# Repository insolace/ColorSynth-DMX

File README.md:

# ColorSynth-DMX<br>
163 DMX RGB pixels for a Burningman 2013 geodesic dome located at camp Morning Cookie<br>
Designed and assembled by Eric Bateman<br>
BMP to DMX mapping done in collaboration with Craig Dorety (http://craigdorety.com/)<br>

ColorSynth DMX RGX pixels are three channel DMX fixtures.  Programmed in assembly, the channels are software defined.

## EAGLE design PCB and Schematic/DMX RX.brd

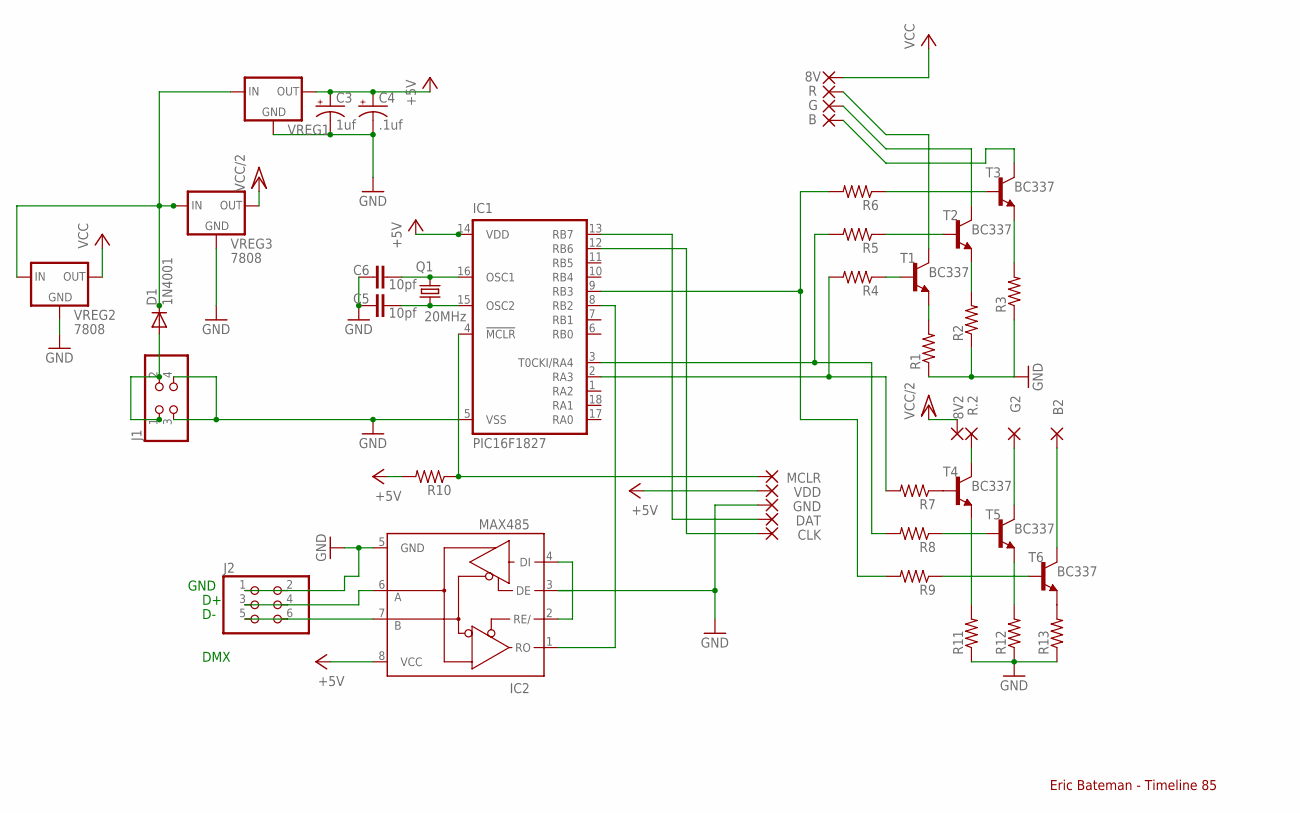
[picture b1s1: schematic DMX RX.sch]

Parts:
8V, 8V2: 2,15/1,0
B, B2: 2,15/1,0
C3: 1uf; E2,5-7
C4: .1uf; E2,5-7
C5, C6: 10pf; C5B3.5
CLK: 1,6/0,8
D1: 1N4001; DIODE-1N4001
DAT: 1,6/0,8
G, G2: 2,15/1,0
GND: 1,6/0,8
IC1: PIC16F1827; DIL18
IC2: MAX485; DIL08
J1: PINHD-2X2/90; 2X02/90
J2: PINHD-2X3/90; 2X03/90
MCLR: 1,6/0,8
Q1: 20MHz; HC49/S
R, R.2: 2,15/1,0
R1, R2, R3, R11, R12, R13: R-US_0411/12; 0411/12
R4, R5, R6, R7, R8, R9, R10: R-US_0204/7; 0204/7
T1, T2, T3, T4, T5, T6: BC337; TO92
VDD: 1,6/0,8
VREG1: 78LXX
VREG2, VREG3: 7808; 78XXS

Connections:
+5V: C3.+, C4.+, IC1.14 (VDD), IC2.8 (VCC), R10.2, VDD.1, VREG1.OUT
+12V: D1.C, VREG1.IN, VREG2.IN, VREG3.IN
A: IC2.6 (A), J2.3, J2.4
B: IC2.7 (B), J2.5, J2.6
CLK: CLK.1, IC1.12 (RB6)
DAT: DAT.1, IC1.13 (RB7)
DC-IN: D1.A, J1.1, J1.2
GND: C3.-, C4.-, C5.2, C6.2, GND.1, IC1.5 (VSS), IC2.2 (RE/), IC2.3 (DE), IC2.4 (DI), IC2.5 (GND), J1.3, J1.4, J2.1, J2.2, R1.1, R2.1, R3.1, R11.1, R12.1, R13.1, VREG1.GND, VREG2.GND, VREG3.GND
MCLR: IC1.4 (!MCLR), MCLR.1, R10.1
unnamed: R6.1, T3.2 (B)
unnamed: R3.2, T3.1 (E)
unnamed: R1.2, T1.1 (E)
unnamed: C6.1, IC1.16 (OSC1), Q1.1
unnamed: C5.1, IC1.15 (OSC2), Q1.2
unnamed: IC1.2 (RA3), R4.2, R7.2
unnamed: IC1.3 (T0CKI/RA4), R5.2, R8.2
unnamed: IC1.9 (RB3), R6.2, R9.2
unnamed: R5.1, T2.2 (B)
unnamed: R4.1, T1.2 (B)
unnamed: R.1, T1.3 (C)
unnamed: G.1, T2.3 (C)
unnamed: R2.2, T2.1 (E)
unnamed: R7.1, T4.2 (B)
unnamed: R13.2, T6.1 (E)
unnamed: R12.2, T5.1 (E)
unnamed: R11.2, T4.1 (E)
unnamed: R9.1, T6.2 (B)
unnamed: R8.1, T5.2 (B)
unnamed: G2.1, T5.3 (C)
unnamed: B2.1, T6.3 (C)
unnamed: R.2.1, T4.3 (C)
unnamed: B.1, T3.3 (C)
RX: IC1.8 (RB2), IC2.1 (RO)
VCC: 8V.1, VREG2.OUT
VCC/2: 8V2.1, VREG3.OUT

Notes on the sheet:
GND
DMX
Eric Bateman - Timeline 85

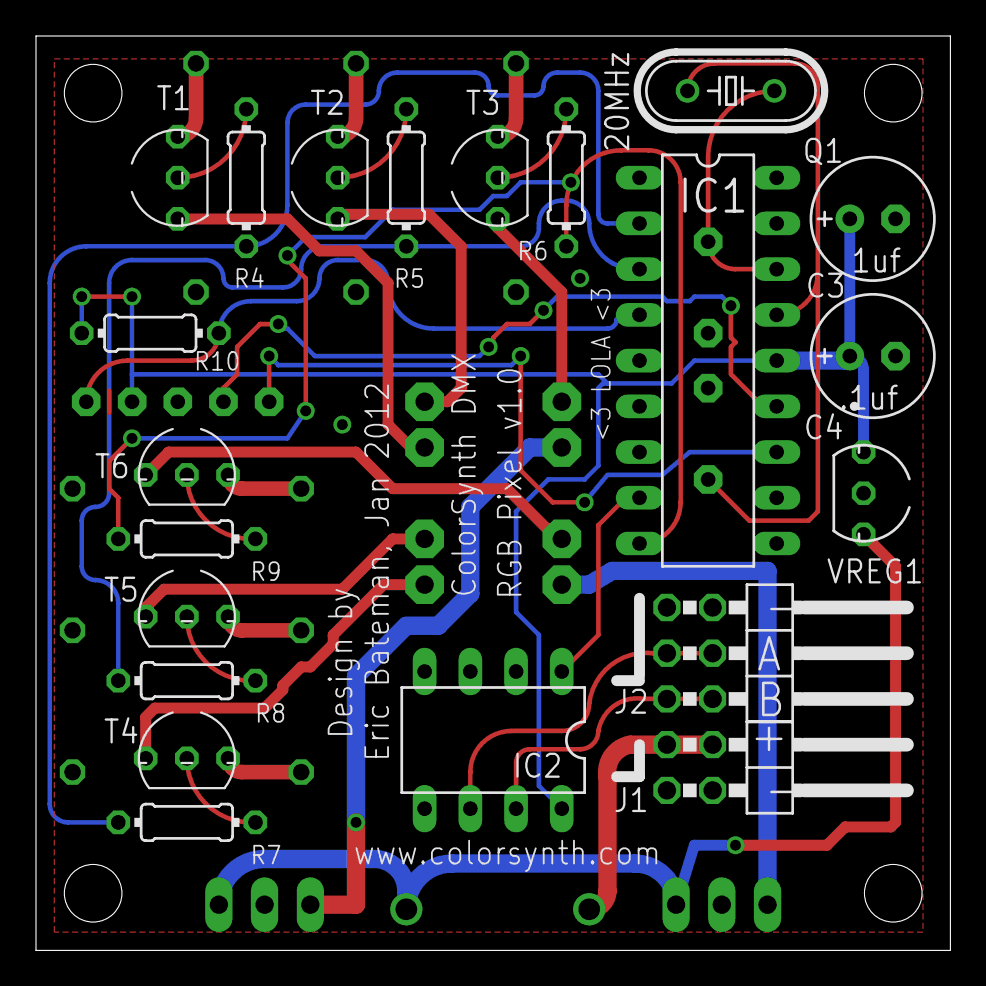
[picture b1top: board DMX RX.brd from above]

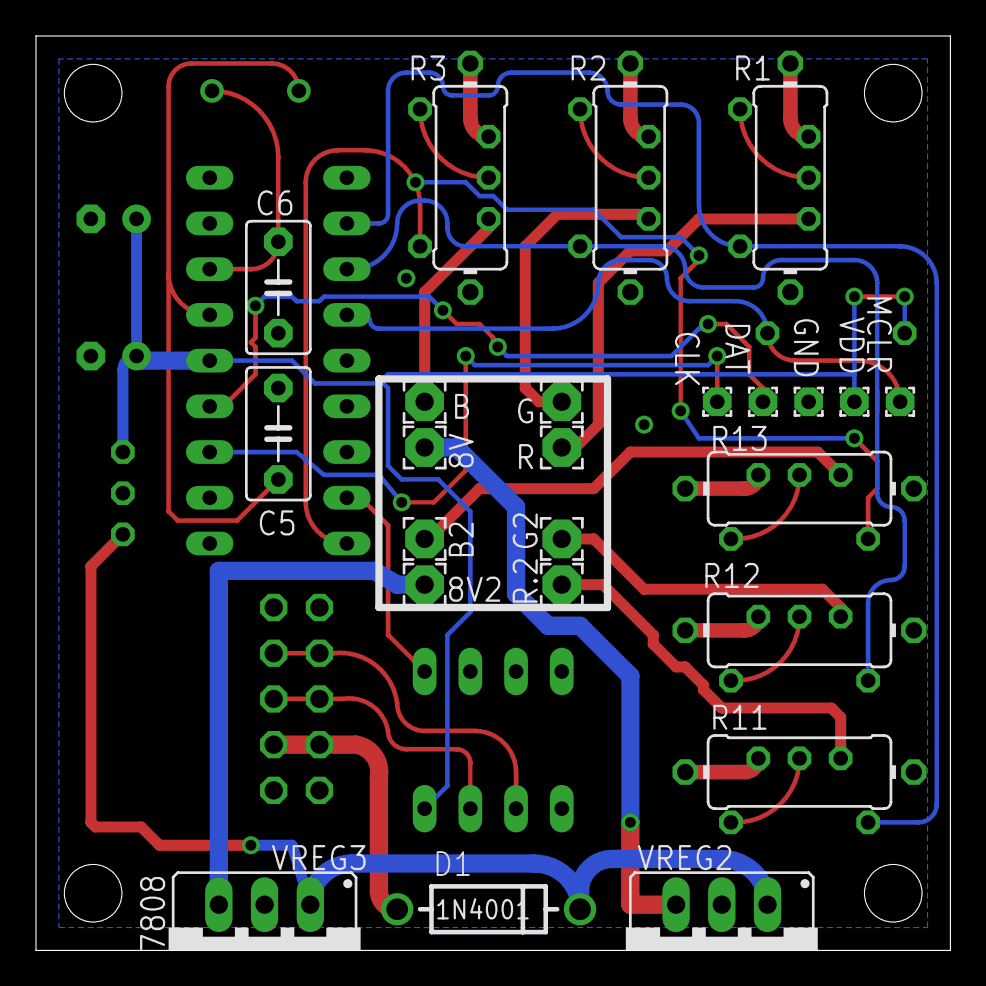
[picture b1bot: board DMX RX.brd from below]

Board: 2 copper layers, 50.8 x 50.8 mm, 45 parts (24 on the bottom side), 35 nets.

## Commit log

2019-09-16 Source and PCB upload
    Initial upload
2020-03-12 Add graphics
2020-03-12 Add Arduino SD sketch
